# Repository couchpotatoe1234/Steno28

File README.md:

# Steno28
A simple hand soldered stenography keyboard with 28 keys. I made this keyboard because I find Stenography keboards interesting and I decided to try making one myself. The PCB is relatively simple, being designed in KiCAD and using the Raspberry Pi Pico RP2040 to connect to the computer.  I didn't bother attempting onboard programming, because that would require attempting to code every single chord I would ever want to type. Rather, I will be using Plover (https://opensteno.org/plover/) that will translate the chords into words. The case is pretty simple, with the PCB just directly screwed on to the case, making it seem as if theres almost no case. It is not supposed to have a plate and is supposed to have a sort of "open-air" PCB. Its really just there to protect the wiring. It will look something like this (sry about the badly rendered keycaps...)  I designed the case in Onshape:https://cad.onshape.com/documents/53637eff7d4d43c451aa77bb/w/a1ff151550c121314276b672/e/7c0bff2a6c8d979b5125e58d?renderMode=2&uiState=69fb53bf7ce38d7c472fc839

Heres the BOM:

| Name                          | Description                                          | Quantity | Total Cost (USD) | Link                                                                                                                                                                                                                                                                                                                                                                                                                                                                                                                                                                                                                                                            | Distributor |
|-------------------------------|------------------------------------------------------|----------|------------------|-----------------------------------------------------------------------------------------------------------------------------------------------------------------------------------------------------------------------------------------------------------------------------------------------------------------------------------------------------------------------------------------------------------------------------------------------------------------------------------------------------------------------------------------------------------------------------------------------------------------------------------------------------------------|-------------|
| PCB                           | Main Component                                       | 1        | 11-12            | https://jlcpcb.com                                                                                                                                                                                                                                                                                                                                                                                                                                                                                                                                                                                                                                              | JLCPCB      |
| Gateron Milky Yellow switches | Key switches for the keyboard                        | 3        | 5-7              | https://www.aliexpress.us/item/3256808155159388.html?spm=a2g0o.productlist.main.2.29fc5sI25sI2z7&algo_pvid=28f7924a-df27-4111-9f3f-13078be8b6a4&algo_exp_id=28f7924a-df27-4111-9f3f-13078be8b6a4-1&pdp_ext_f=%7B%22order%22%3A%2213%22%2C%22eval%22%3A%221%22%2C%22fromPage%22%3A%22search%22%7D&pdp_npi=6%40dis%21USD%216.29%215.81%21%21%2142.24%2139.04%21%402103128917862359623133668e1044%2112000044659334551%21sea%21US%210%21ABX%211%210%21n_tag%3A-29910%3Bd%3Ad289bca0%3Bm03_new_user%3A-29895%3BpisId%3A5000000210913316&curPageLogUid=SlbQkXYMbyc8&utparam-url=scene%3Asearch%7Cquery_from%3A%7Cx_object_id%3A1005008341474140%7C_p_origin_prod%3A   | Aliexpress  |
| M3 screws, 25mm long          | to connect the PCB to the case                       | 2        | 2-3              | https://www.aliexpress.us/item/3256807894724568.html?spm=a2g0o.productlist.main.8.519aeGyIeGyIWi&algo_pvid=e25d90af-db15-4d30-8383-15a65a8c789b&algo_exp_id=e25d90af-db15-4d30-8383-15a65a8c789b-37&pdp_ext_f=%7B%22order%22%3A%223213%22%2C%22eval%22%3A%221%22%2C%22fromPage%22%3A%22search%22%7D&pdp_npi=6%40dis%21USD%212.20%210.99%21%21%2114.74%216.61%21%402103292b17862358008321168e0d1c%2112000043591225532%21sea%21US%210%21ABX%211%210%21n_tag%3A-29910%3Bd%3Ad289bca0%3Bm03_new_user%3A-29895%3BpisId%3A5000000210792318&curPageLogUid=Axerb0q0V5Js&utparam-url=scene%3Asearch%7Cquery_from%3A%7Cx_object_id%3A1005008081039320%7C_p_origin_prod%3A | Aliexpress  |
| 40 pin header                 | to connect the pi to the PCB. will be split in half. | 1        | 2-5              | https://www.aliexpress.us/item/3256809184452517.html?spm=a2g0o.productlist.main.37.2a7547JV47JVyu&utparam-url=scene%3Asearch%7Cquery_from%3Apc_back_same_best%7Cx_object_id%3A1005009370767269%7C_p_origin_prod%3A&algo_pvid=702d1175-b582-4e95-bcc1-7a7455c9282d&algo_exp_id=702d1175-b582-4e95-bcc1-7a7455c9282d&pdp_ext_f=%7B%22order%22%3A%222216%22%2C%22fromPage%22%3A%22search%22%7D&pdp_npi=6%40dis%21USD%214.37%211.99%21%21%2129.36%2113.40%21%40210328df17862995257677221e0cb8%2112000048894384146%21sea%21US%217546124065%21X%211%210%21n_tag%3A-29911%3Bd%3Ad289bca0%3Bm03_new_user%3A-29895%3BpisId%3A5000000214292494&gatewayAdapt=4itemAdapt    | Aliexpress  |
| Raspberry Pi Pico RP2040      | the main microcontroller                             | 1        | 2-4              | hhttps://www.aliexpress.us/item/3256806652932348.html?spm=a2g0o.productlist.main.2.cdd368b4mVk5Dn&algo_pvid=7f9073cf-37a9-4852-8278-f151c6d7a7c5&algo_exp_id=7f9073cf-37a9-4852-8278-f151c6d7a7c5-1&pdp_ext_f=%7B%22order%22%3A%221936%22%2C%22eval%22%3A%221%22%2C%22fromPage%22%3A%22search%22%7D&pdp_npi=6%40dis%21USD%213.72%210.99%21%21%2124.97%216.65%21%402103292b17862357368798295e1096%2112000056467786851%21sea%21US%210%21ABX%211%210%21n_tag%3A-29910%3Bd%3Ad289bca0%3Bm03_new_user%3A-29895%3BpisId%3A5000000210792318&curPageLogUid=E4APFhff29iy&utparam-url=scene%3Asearch%7Cquery_from%3A%7Cx_object_id%3A1005006839247100%7C_p_origin_prod%3A | Aliexpress  |
| 1N4148 diodes                 | diodes for the matrix                                | 28       | 1-3              | https://www.aliexpress.us/item/3256809192784213.html?spm=a2g0o.productlist.main.2.3d7d2d8br7X8gQ&algo_pvid=b896ad33-f0bc-4a35-950a-bbb58163a61a&algo_exp_id=b896ad33-f0bc-4a35-950a-bbb58163a61a-1&pdp_ext_f=%7B%22order%22%3A%22484%22%2C%22eval%22%3A%221%22%2C%22fromPage%22%3A%22search%22%7D&pdp_npi=6%40dis%21USD%213.83%211.92%21%21%2125.69%2112.84%21%402101ca9517862996536951721e2253%2112000048926087942%21sea%21US%217546124065%21X%211%210%21n_tag%3A-29911%3Bd%3Ad289bca0%3Bm03_new_user%3A-29895&curPageLogUid=z294DkysUBGn&utparam-url=scene%3Asearch%7Cquery_from%3A%7Cx_object_id%3A1005009379098965%7C_p_origin_prod%3A                      | Aliexpress  |

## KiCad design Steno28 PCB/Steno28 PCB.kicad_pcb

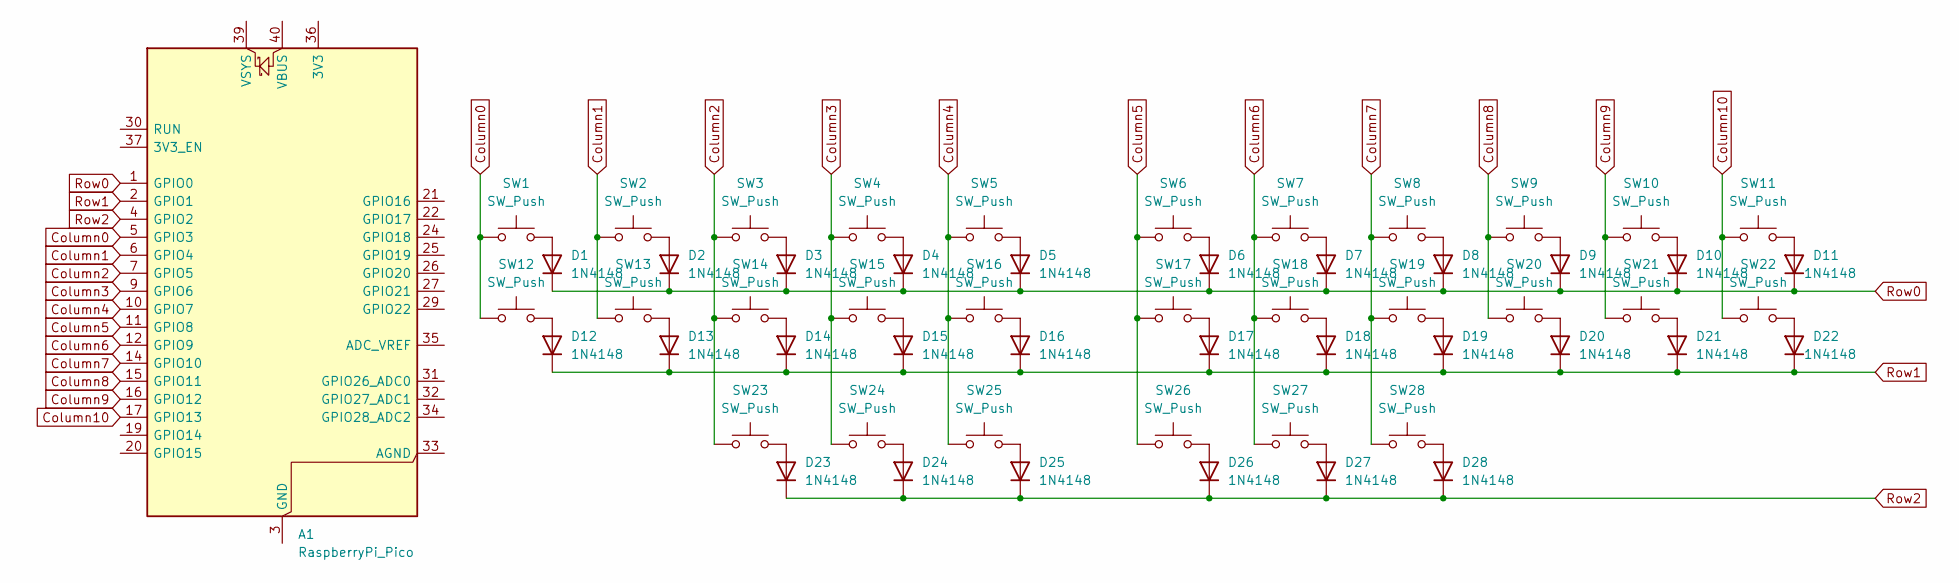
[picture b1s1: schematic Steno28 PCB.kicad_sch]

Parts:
A1: RaspberryPi_Pico; RaspberryPi_Pico_Common_Unspecified
D1, D2, D3, D4, D5, D6, D7, D8, D9, D10, D11, D12, D13, D14, D15, D16, D17, D18, D19, D20, D21, D22, D23, D24, D25, D26, D27, D28: 1N4148; D_DO-35_SOD27_P7.62mm_Horizontal
SW1, SW2, SW3, SW4, SW5, SW6, SW7, SW8, SW9, SW10, SW11, SW12, SW13, SW14, SW15, SW16, SW17, SW18, SW19, SW20, SW21, SW22, SW23, SW24, SW25, SW26, SW27, SW28: SW_Push; SW_Cherry_MX_1.00u_PCB

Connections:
Column0: A1.5 (GPIO3), SW1.1, SW12.1
Column1: A1.6 (GPIO4), SW2.1, SW13.1
Column2: A1.7 (GPIO5), SW3.1, SW14.1, SW23.1
Column3: A1.9 (GPIO6), SW4.1, SW15.1, SW24.1
Column4: A1.10 (GPIO7), SW5.1, SW16.1, SW25.1
Column5: A1.11 (GPIO8), SW6.1, SW17.1, SW26.1
Column6: A1.12 (GPIO9), SW7.1, SW18.1, SW27.1
Column7: A1.14 (GPIO10), SW8.1, SW19.1, SW28.1
Column8: A1.15 (GPIO11), SW9.1, SW20.1
Column9: A1.16 (GPIO12), SW10.1, SW21.1
Column10: A1.17 (GPIO13), SW11.1, SW22.1
unnamed: A1.3 (GND), A1.8 (GND), A1.13 (GND), A1.18 (GND), A1.23 (GND), A1.28 (GND), A1.38 (GND)
unnamed: D1.2 (A), SW1.2
unnamed: D2.2 (A), SW2.2
unnamed: D3.2 (A), SW3.2
unnamed: D4.2 (A), SW4.2
unnamed: D5.2 (A), SW5.2
unnamed: D6.2 (A), SW6.2
unnamed: D7.2 (A), SW7.2
unnamed: D8.2 (A), SW8.2
unnamed: D9.2 (A), SW9.2
unnamed: D10.2 (A), SW10.2
unnamed: D11.2 (A), SW11.2
unnamed: D12.2 (A), SW12.2
unnamed: D13.2 (A), SW13.2
unnamed: D14.2 (A), SW14.2
unnamed: D15.2 (A), SW15.2
unnamed: D16.2 (A), SW16.2
unnamed: D17.2 (A), SW17.2
unnamed: D18.2 (A), SW18.2
unnamed: D19.2 (A), SW19.2
unnamed: D20.2 (A), SW20.2
unnamed: D21.2 (A), SW21.2
unnamed: D22.2 (A), SW22.2
unnamed: D23.2 (A), SW23.2
unnamed: D24.2 (A), SW24.2
unnamed: D25.2 (A), SW25.2
unnamed: D26.2 (A), SW26.2
unnamed: D27.2 (A), SW27.2
unnamed: D28.2 (A), SW28.2
Row0: A1.1 (GPIO0), D1.1 (K), D2.1 (K), D3.1 (K), D4.1 (K), D5.1 (K), D6.1 (K), D7.1 (K), D8.1 (K), D9.1 (K), D10.1 (K), D11.1 (K)
Row1: A1.2 (GPIO1), D12.1 (K), D13.1 (K), D14.1 (K), D15.1 (K), D16.1 (K), D17.1 (K), D18.1 (K), D19.1 (K), D20.1 (K), D21.1 (K), D22.1 (K)
Row2: A1.4 (GPIO2), D23.1 (K), D24.1 (K), D25.1 (K), D26.1 (K), D27.1 (K), D28.1 (K)

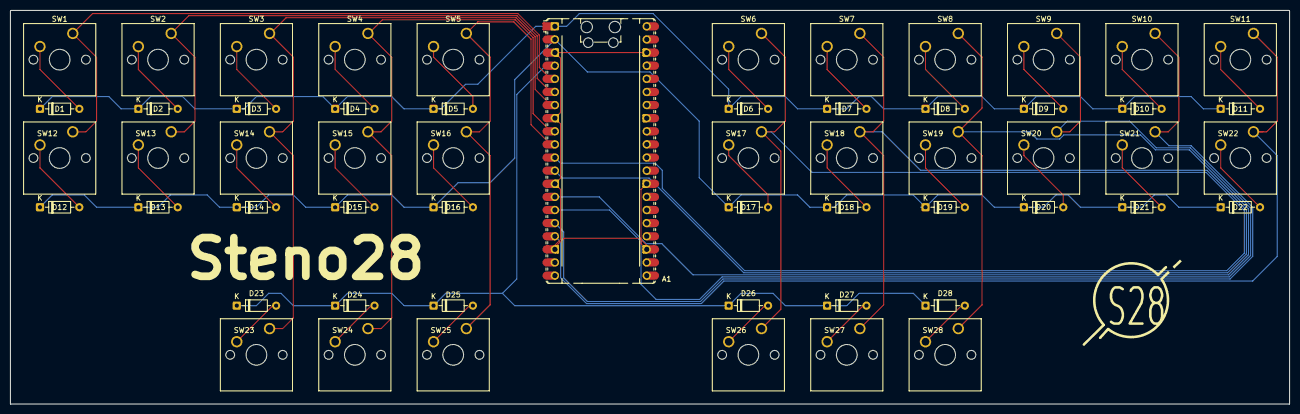
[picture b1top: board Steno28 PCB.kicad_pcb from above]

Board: 2 copper layers, 247.6 x 76.2 mm, 57 parts (0 on the bottom side), 43 nets.

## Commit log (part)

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2026-05-05 firmware, PCB, & Gerbers
2026-05-06 case
2026-05-06 BOM & README
